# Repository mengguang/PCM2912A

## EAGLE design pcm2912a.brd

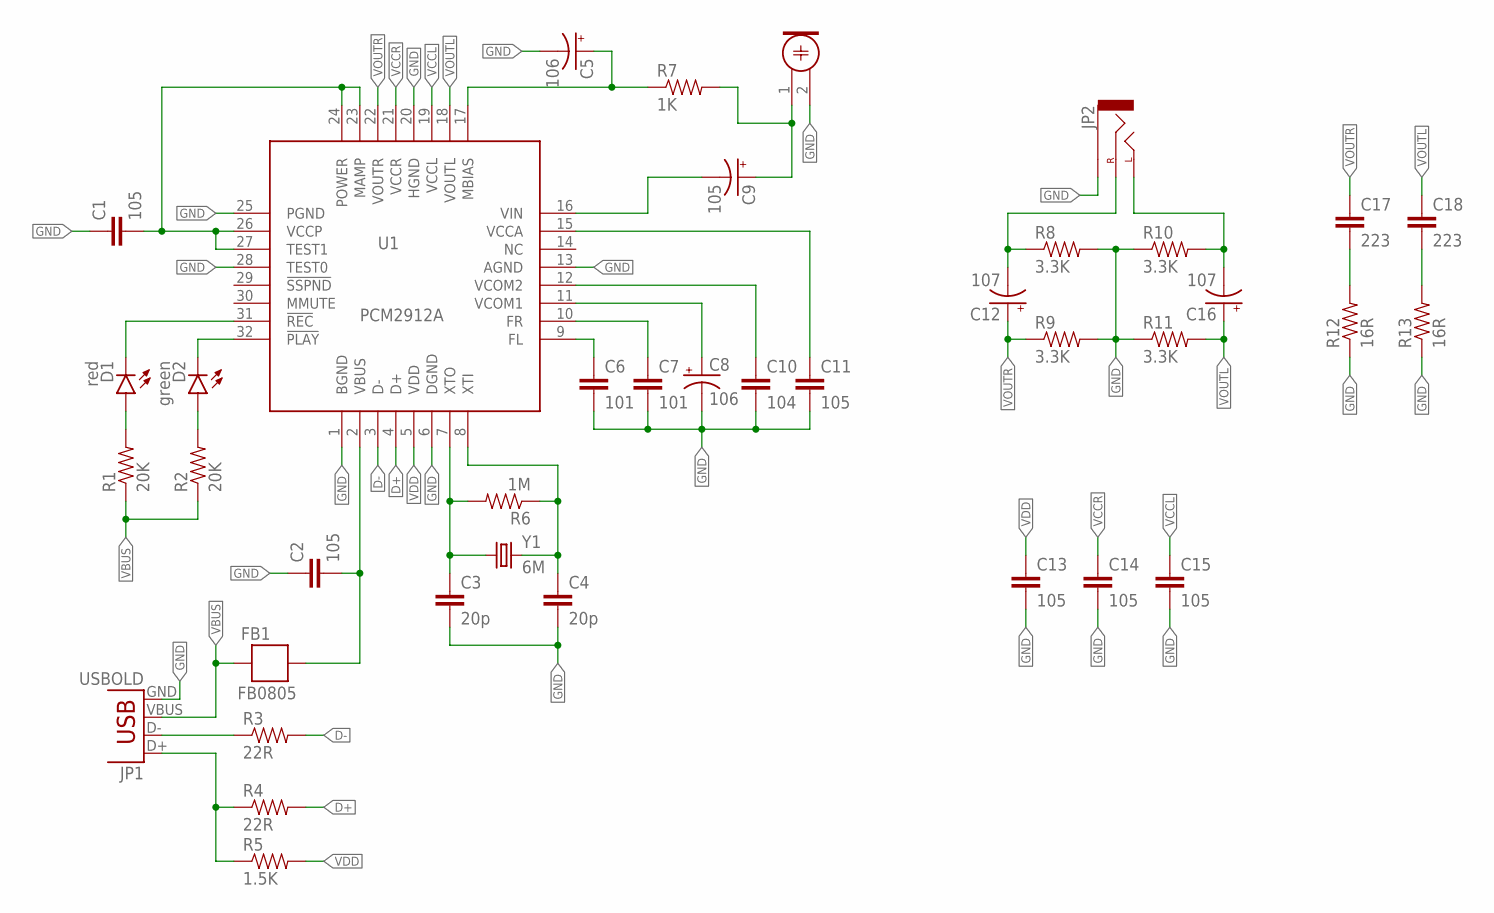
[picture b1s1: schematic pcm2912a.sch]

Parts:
C1, C2, C11, C13, C14, C15: 105; 0402-CAP
C3, C4: 20p; 0402-CAP
C5, C8: 106; EIA3216-KIT
C6, C7: 101; 0402-CAP
C9: 105; EIA3216-KIT
C10: 104; 0402-CAP
C12, C16: 107; EIA3528-KIT
C17, C18: 223; 0402-CAP
D1: red; LED-0603-EASY
D2: green; LED-0603-EASY
FB1: FB0805; 0805
JP1: USBOLD; USB-MINIB-OLD
JP2: AUDIO-JACKAUDIO-JACK-3.5MM-PTH-JLC; AUDIO-JACK-3.5MM-PTH-JLC
M1: ELECTRET_MICROPHON-WM-62PC/62PK; WM-62PC/62PK
R1, R2: 20K; 0402-RES
R3, R4: 22R; 0402-RES
R5: 1.5K; 0402-RES
R6: 1M; 0402-RES
R7: 1K; 0402-RES
R8, R9, R10, R11: 3.3K; 0402-RES
R12, R13: 16R; 0402-RES
U1: PCM2912A; TQFP32-08
Y1: 6M; HC49US

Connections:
D+: R4.2, U1.4 (D+)
D-: R3.2, U1.3 (D-)
GND: C1.1, C2.1, C3.2, C4.2, C5.C (-), C6.2, C7.2, C8.C (-), C10.2, C11.2, C13.2, C14.2, C15.2, JP1.GND, JP2.P$1 (SLEEVE), M1.2, R8.2, R9.2, R10.1, R11.1, R12.1, R13.1, U1.1 (BGND), U1.6 (DGND), U1.13 (AGND), U1.20 (HGND), U1.25 (PGND), U1.28 (TEST0)
unnamed: C6.1, U1.9 (FL)
unnamed: C7.1, U1.10 (FR)
unnamed: C8.A (+), U1.11 (VCOM1)
unnamed: C10.1, U1.12 (VCOM2)
unnamed: C11.1, U1.15 (VCCA)
unnamed: D1.- (C), U1.31 (!REC)
unnamed: D2.- (C), U1.32 (!PLAY)
unnamed: D1.+ (A), R1.2
unnamed: D2.+ (A), R2.2
unnamed: C3.1, R6.2, U1.7 (XTO), Y1.1
unnamed: C4.1, R6.1, U1.8 (XTI), Y1.2
unnamed: JP1.D-, R3.1
unnamed: JP1.D+, R4.1, R5.1
unnamed: C9.C (-), U1.16 (VIN)
unnamed: C2.2, FB1.1, U1.2 (VBUS)
unnamed: C12.C (-), JP2.P$2 (RIGHT), R8.1
unnamed: C1.2, U1.23 (MAMP), U1.24 (POWER), U1.26 (VCCP), U1.27 (TEST1)
unnamed: C9.A (+), M1.1, R7.2
unnamed: C5.A (+), R7.1, U1.17 (MBIAS)
unnamed: C16.C (-), JP2.P$3 (LEFT), R10.2
unnamed: C17.2, R12.2
unnamed: C18.2, R13.2
VBUS: FB1.2, JP1.VBUS, R1.1, R2.1
VCCL: C15.1, U1.19 (VCCL)
VCCR: C14.1, U1.21 (VCCR)
VDD: C13.1, R5.2, U1.5 (VDD)
VOUTL: C16.A (+), C18.1, R11.2, U1.18 (VOUTL)
VOUTR: C12.A (+), C17.1, R9.1, U1.22 (VOUTR)

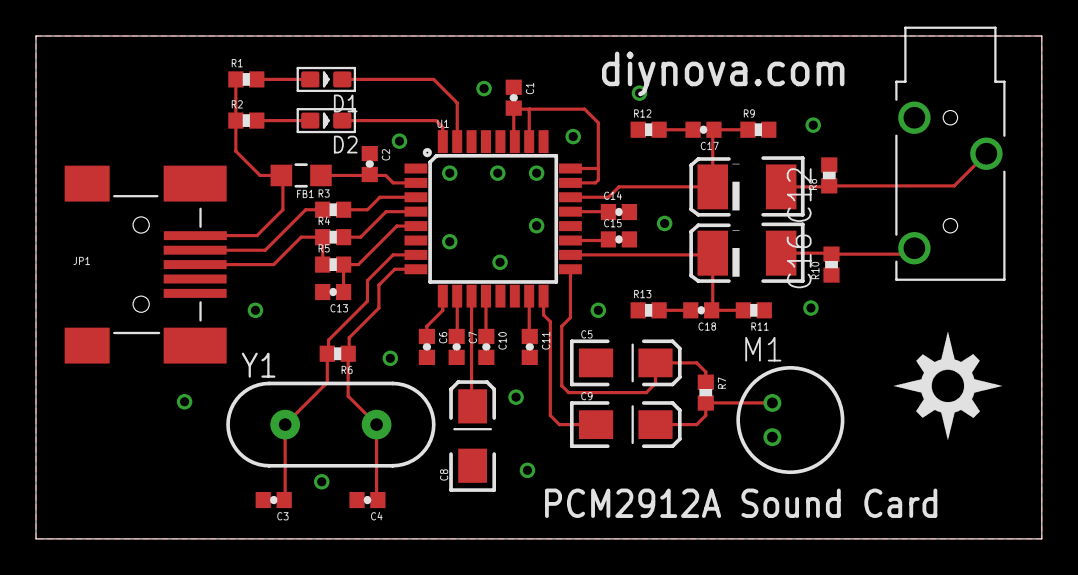
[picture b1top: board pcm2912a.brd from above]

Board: 2 copper layers, 55.9 x 27.9 mm, 40 parts (0 on the bottom side), 31 nets.

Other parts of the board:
U$1: DIYNOVA_LOGO

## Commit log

2020-07-01 import from old backup
